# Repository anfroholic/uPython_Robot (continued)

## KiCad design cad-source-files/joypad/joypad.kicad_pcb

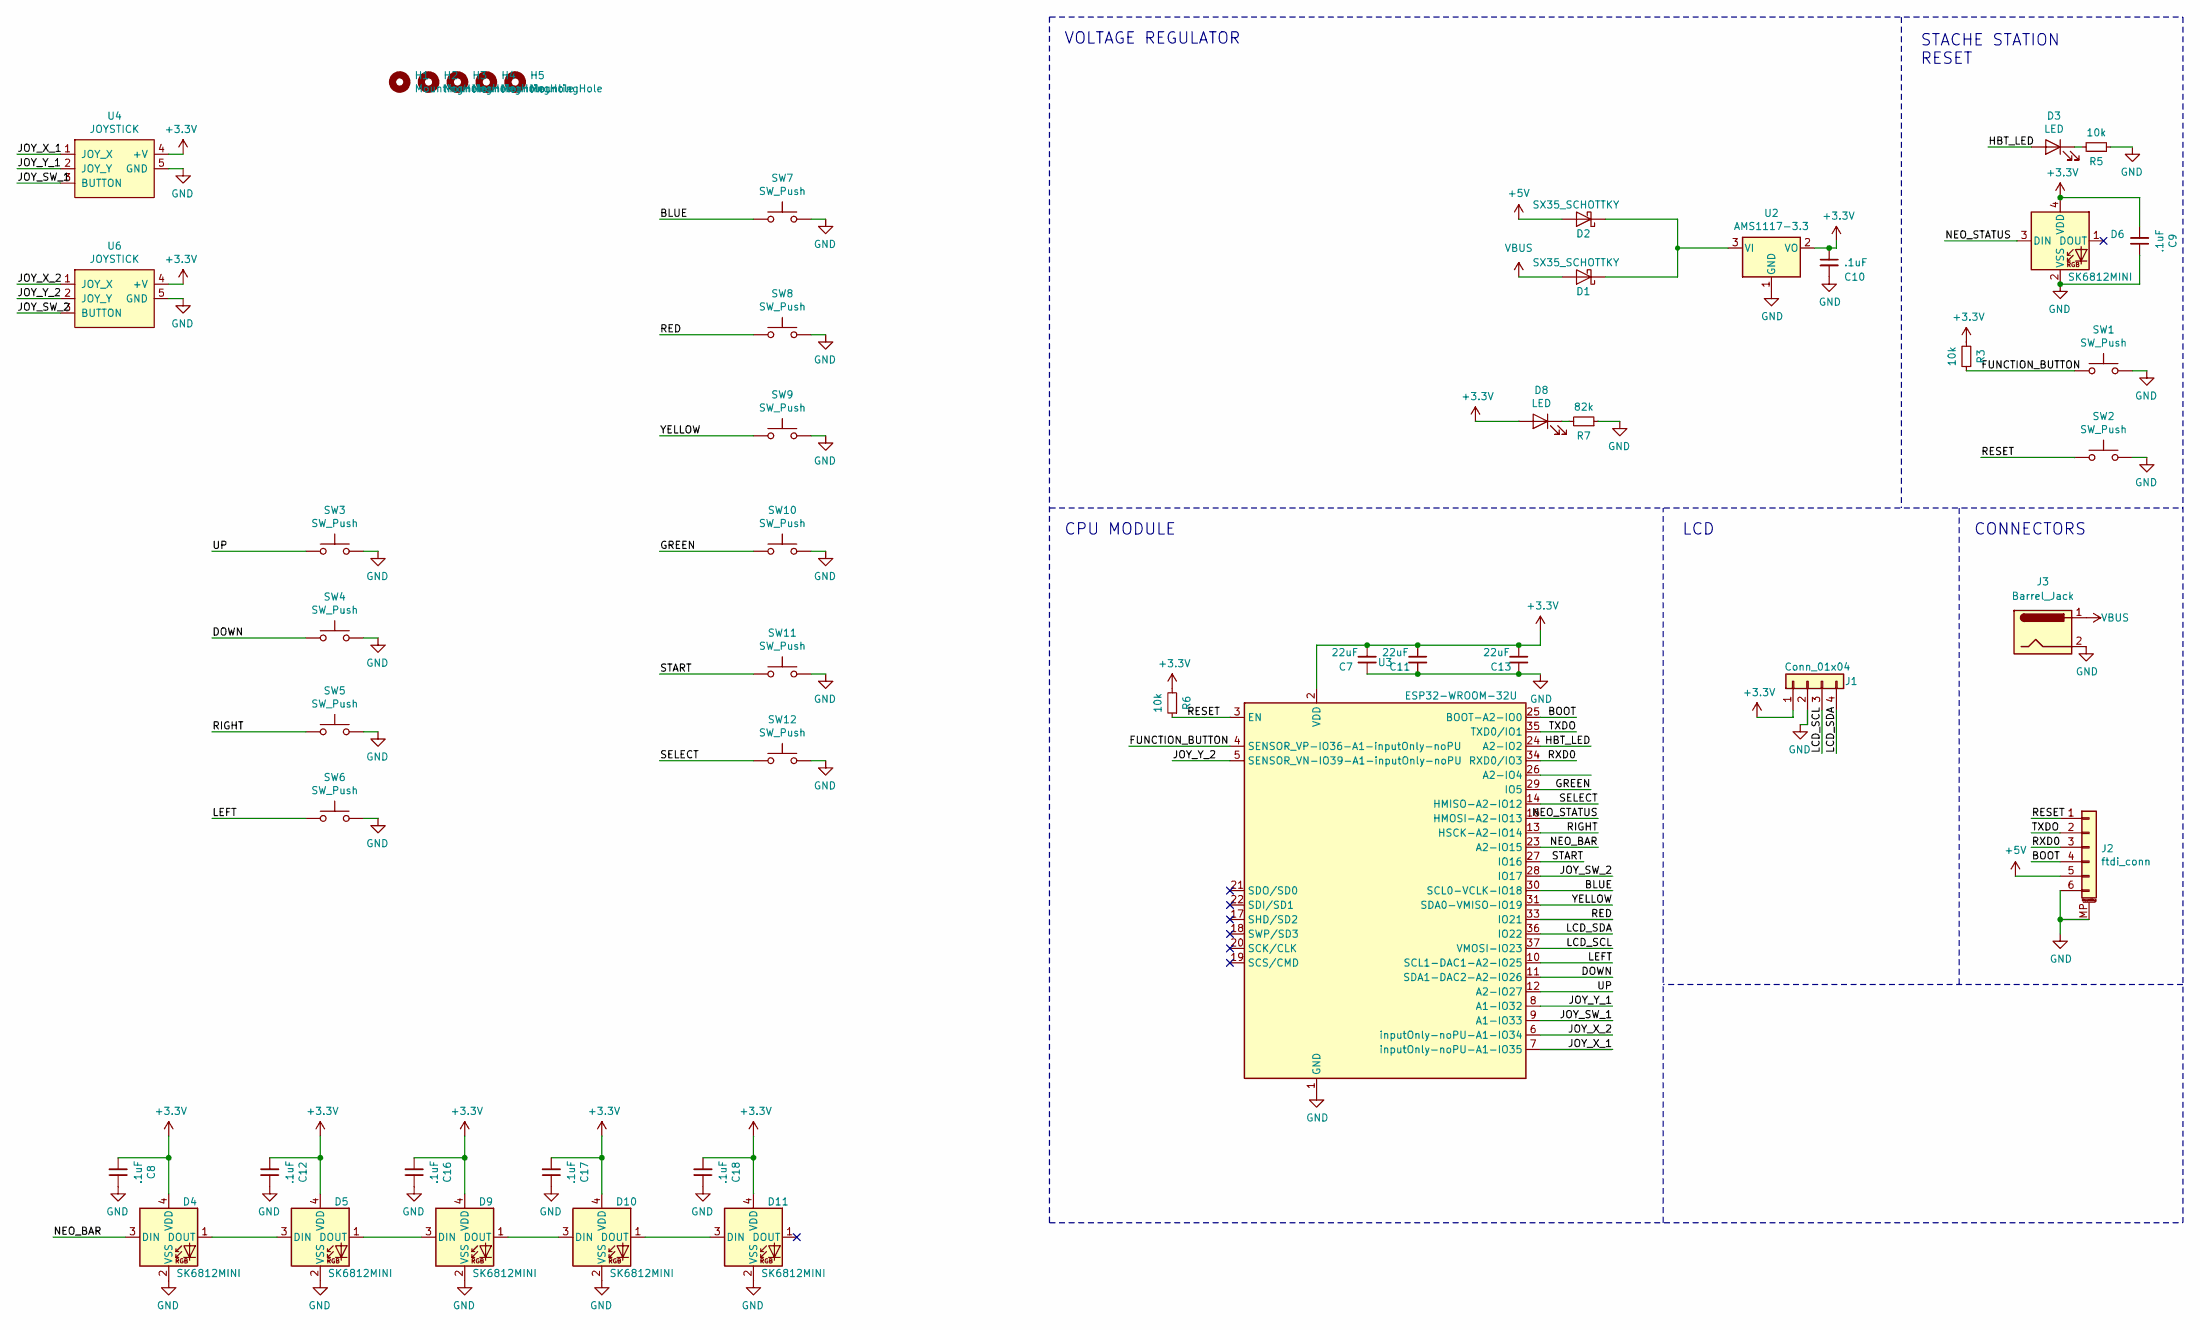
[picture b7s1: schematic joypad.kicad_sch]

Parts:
C7, C11, C13: 22uF; C_0805_2012Metric
C8, C9, C10, C12, C16, C17, C18: .1uF; C_0603_1608Metric
D1, D2: SX35_SCHOTTKY; D_SMA
D3, D8: LED; LED_0603_1608Metric
D4, D5, D6, D9, D10, D11: SK6812MINI; LED_SK6812MINI_PLCC4_3.5x3.5mm_P1.75mm
H1, H2, H3, H4, H5: MountingHole; MountingHole_2.5mm_Pad
J1: Conn_01x04; PinSocket_1x04_P2.54mm_Vertical
J2: ftdi_conn; JST_SH_SM06B-SRSS-TB_1x06-1MP_P1.00mm_Horizontal
J3: Barrel_Jack; BarrelJack_Horizontal
R3, R5, R6: 10k; R_0603_1608Metric
R7: 82k; R_0603_1608Metric
SW1, SW2, SW3, SW4, SW5, SW6, SW11, SW12: SW_Push; SWITCH_2x3_SMD_TACTILE_GREEN
SW7, SW8, SW9, SW10: SW_Push; 12mm_pushbutton
U2: AMS1117-3.3; SOT-223-3_TabPin2
U3: ESP32-WROOM-32U; ESP32-WROOM-32U_evezor
U4, U6: JOYSTICK

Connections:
+3V3: C7.1, C8.2, C9.2, C10.1, C11.1, C12.2, C13.1, C16.2, C17.2, C18.2, D4.4 (VDD), D5.4 (VDD), D6.4 (VDD), D8.2 (A), D9.4 (VDD), D10.4 (VDD), D11.4 (VDD), J1.1, R3.2, R6.2, U2.2 (VO), U3.2 (VDD), U4.4 (+V), U6.4 (+V)
+5V: D2.2 (A), J2.5
/BLUE: SW7.1, U3.30 (SCL0-VCLK-IO18)
/BOOT: J2.4, U3.25 (BOOT-A2-IO0)
/DOWN: SW4.1, U3.11 (SDA1-DAC2-A2-IO26)
/FUNCTION_BUTTON: R3.1, SW1.1, U3.4 (SENSOR_VP-IO36-A1-inputOnly-noPU)
/GREEN: SW10.1, U3.29 (IO5)
/HBT_LED: D3.2 (A), U3.24 (A2-IO2)
/JOY_SW_1: U3.9 (A1-IO33), U4.3 (BUTTON)
/JOY_SW_2: U3.28 (IO17), U6.3 (BUTTON)
/JOY_X_1: U3.7 (inputOnly-noPU-A1-IO35), U4.1 (JOY_X)
/JOY_X_2: U3.6 (inputOnly-noPU-A1-IO34), U6.1 (JOY_X)
/JOY_Y_1: U3.8 (A1-IO32), U4.2 (JOY_Y)
/JOY_Y_2: U3.5 (SENSOR_VN-IO39-A1-inputOnly-noPU), U6.2 (JOY_Y)
/LCD_SCL: J1.3, U3.37 (VMOSI-IO23)
/LCD_SDA: J1.4, U3.36 (IO22)
/LEFT: SW6.1, U3.10 (SCL1-DAC1-A2-IO25)
/NEO_BAR: D4.3 (DIN), U3.23 (A2-IO15)
/NEO_STATUS: D6.3 (DIN), U3.16 (HMOSI-A2-IO13)
/RED: SW8.1, U3.33 (IO21)
/RESET: J2.1, R6.1, SW2.1, U3.3 (EN)
/RIGHT: SW5.1, U3.13 (HSCK-A2-IO14)
/RXD0: J2.3, U3.34 (RXD0/IO3)
/SELECT: SW12.1, U3.14 (HMISO-A2-IO12)
/START: SW11.1, U3.27 (IO16)
/TXDO: J2.2, U3.35 (TXD0/IO1)
/UP: SW3.1, U3.12 (A2-IO27)
/YELLOW: SW9.1, U3.31 (SDA0-VMISO-IO19)
GND: C7.2, C8.1, C9.1, C10.2, C11.2, C12.1, C13.2, C16.1, C17.1, C18.1, D4.2 (VSS), D5.2 (VSS), D6.2 (VSS), D9.2 (VSS), D10.2 (VSS), D11.2 (VSS), J1.2, J2.6, J2.MP (MountPin), J3.2, R5.1, R7.1, SW1.2, SW2.2, SW3.2, SW4.2, SW5.2, SW6.2, SW7.2, SW8.2, SW9.2, SW10.2, SW11.2, SW12.2, U2.1 (GND), U3.1 (GND), U3.15 (GND), U3.38 (GND), U3.39 (GND), U4.5 (GND), U6.5 (GND)
unnamed: D1.1 (K), D2.1 (K), U2.3 (VI)
unnamed: D3.1 (K), R5.2
unnamed: D4.1 (DOUT), D5.3 (DIN)
unnamed: D5.1 (DOUT), D9.3 (DIN)
unnamed: D8.1 (K), R7.2
unnamed: D10.1 (DOUT), D11.3 (DIN)
unnamed: D9.1 (DOUT), D10.3 (DIN)
VBUS: D1.2 (A), J3.1

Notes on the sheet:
VOLTAGE REGULATOR
CPU MODULE
LCD
STACHE STATION RESET
CONNECTORS

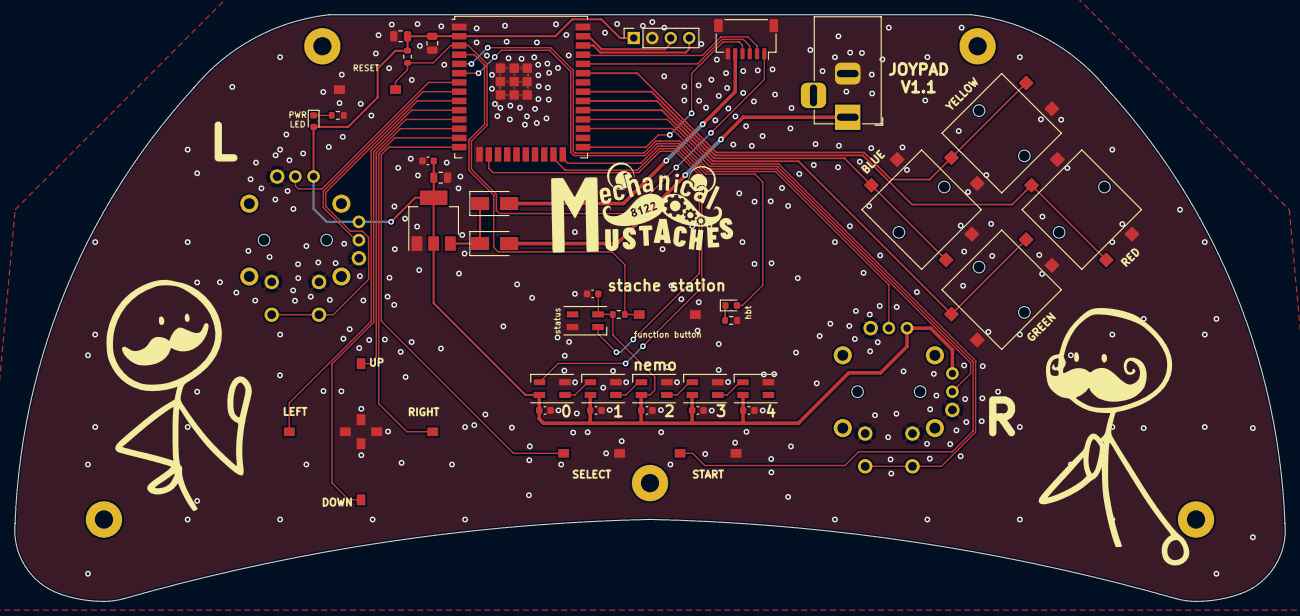
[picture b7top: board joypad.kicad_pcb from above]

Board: 2 copper layers, 174.5 x 80.6 mm, 48 parts (0 on the bottom side), 37 nets.

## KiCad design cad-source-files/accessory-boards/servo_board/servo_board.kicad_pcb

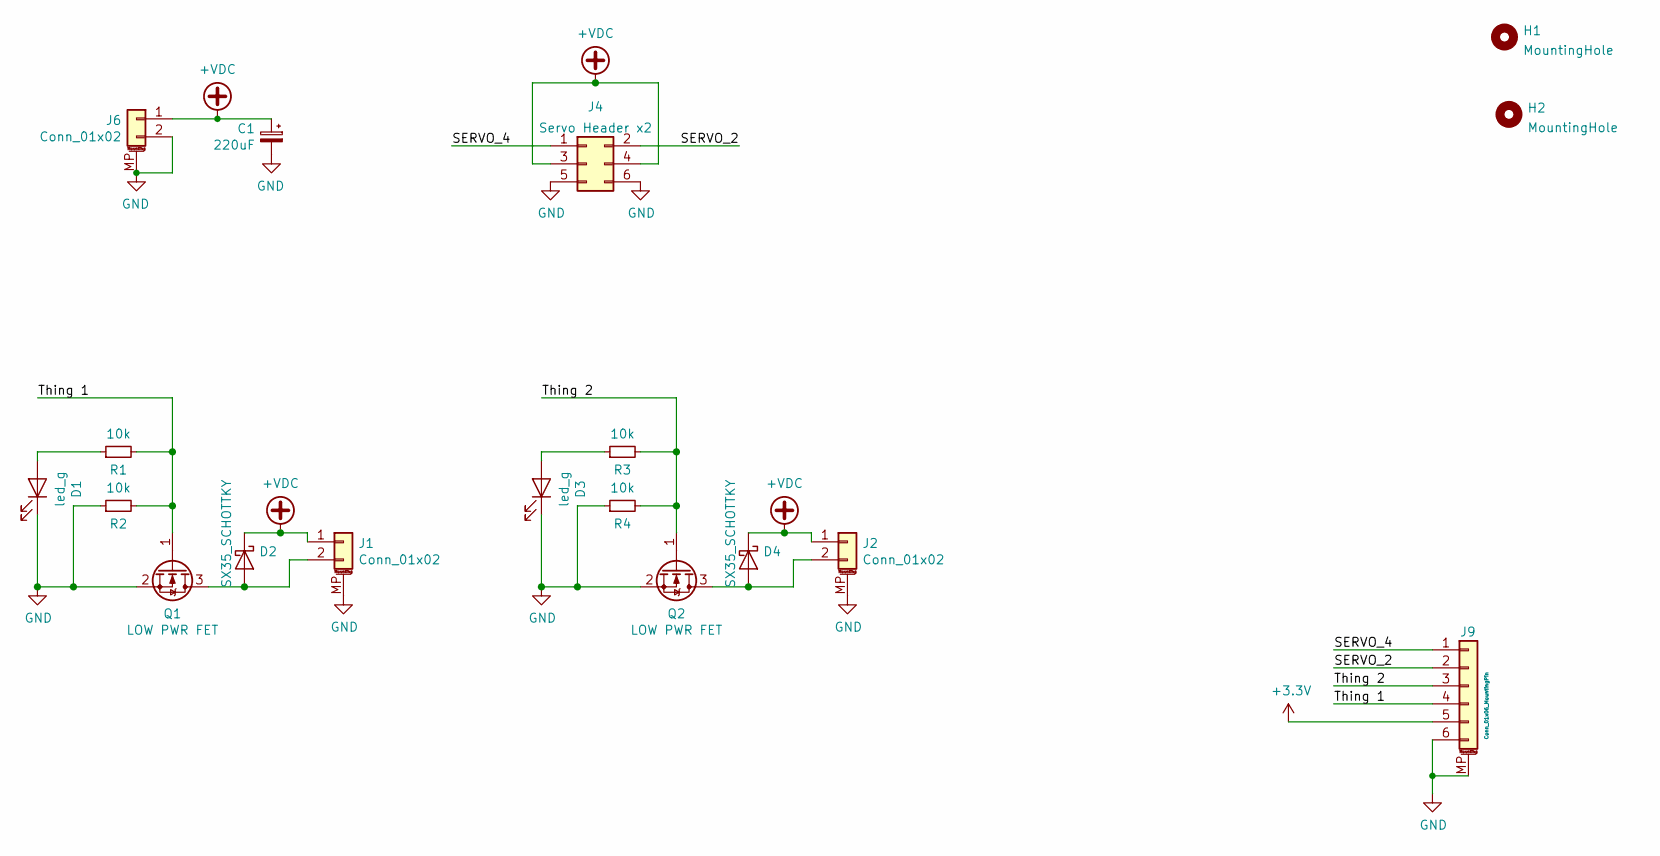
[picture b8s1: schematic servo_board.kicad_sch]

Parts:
C1: 220uF; CP_Elec_8x6.5
D1, D3: led_g; LED_0603_1608Metric
D2, D4: SX35_SCHOTTKY; D_SMA
H1, H2: MountingHole; MountingHole_3.2mm_M3_ISO14580
J1, J2: Conn_01x02; JST_XH_2_VERTICAL
J4: Servo Header x2; PinHeader_2x03_P2.54mm_Vertical_SMD
J6: Conn_01x02; JST_PH_B2B-PH-SM4-TB_1x02-1MP_P2.00mm_Vertical
J9: Conn_01x06_MountingPin; TE_84952-6_1x06-1MP_P1.0mm_Horizontal
Q1, Q2: LOW PWR FET; SOT-23
R1, R2, R3, R4: 10k; R_0603_1608Metric

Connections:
+3V3: J9.5
+VDC: C1.1, D2.1 (K), D4.1 (K), J1.1, J2.1, J4.3, J4.4, J6.1
/SERVO_2: J4.2, J9.2
/SERVO_4: J4.1, J9.1
/Thing 1: J9.4, Q1.1 (G), R1.2, R2.2
/Thing 2: J9.3, Q2.1 (G), R3.2, R4.2
GND: C1.2, D1.1 (K), D3.1 (K), J1.MP (MountPin), J2.MP (MountPin), J4.5, J4.6, J6.2, J6.MP (MountPin), J9.6, J9.MP (MountPin), Q1.2 (S), Q2.2 (S), R2.1, R4.1
unnamed: D1.2 (A), R1.1
unnamed: D2.2 (A), J1.2, Q1.3 (D)
unnamed: D3.2 (A), R3.1
unnamed: D4.2 (A), J2.2, Q2.3 (D)

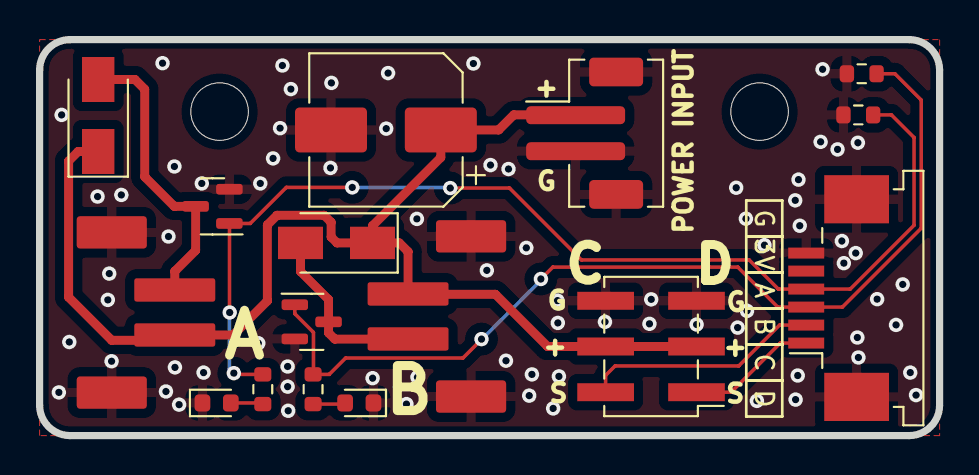
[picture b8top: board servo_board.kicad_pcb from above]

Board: 2 copper layers, 50.0 x 22.0 mm, 18 parts (0 on the bottom side), 10 nets.

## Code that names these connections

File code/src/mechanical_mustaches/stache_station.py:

from machine import Pin
from neopixel import NeoPixel
import uasyncio as asyncio


class StacheStation:
    def __init__(self, *, hbt_led, function_button, neo_status, **kwargs):
        self.hbt_led = Pin(hbt_led, Pin.OUT)
        self.function_button = Pin(function_button, Pin.IN)
        self.neo = NeoPixel(Pin(neo_status, Pin.OUT), 1)
        self.neo[0] = (0,0,0)
        self.neo.write()


    def check(self):
        if not self.function_button.value():
            print('function button pressed')
            self.neo[0] = (4,12,0)
            self.neo.write()
            raise KeyboardInterrupt
        
    async def hbt(self):
        while True:
            self.hbt_led.value(not self.hbt_led.value())
            await asyncio.sleep_ms(500)
        
    def fill(self, r, g, b):
        self.neo[0] = (r,g,b)
        self.neo.write()
        
    
class FakeStation:
    def __init__(self):
        pass
    
    def check(*args, **kwargs):
        pass
    
    def fill(*args, **kwargs):
        pass

    

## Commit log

2022-12-16 init
